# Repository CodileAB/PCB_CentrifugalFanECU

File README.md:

ECU for the Centrifugal Fan Module
==================================

This is the KiCad project for the ECU for the Centrifugal Fan module.

Licence
-------

Licenced under the CERN Open Hardware Licence v1.2.

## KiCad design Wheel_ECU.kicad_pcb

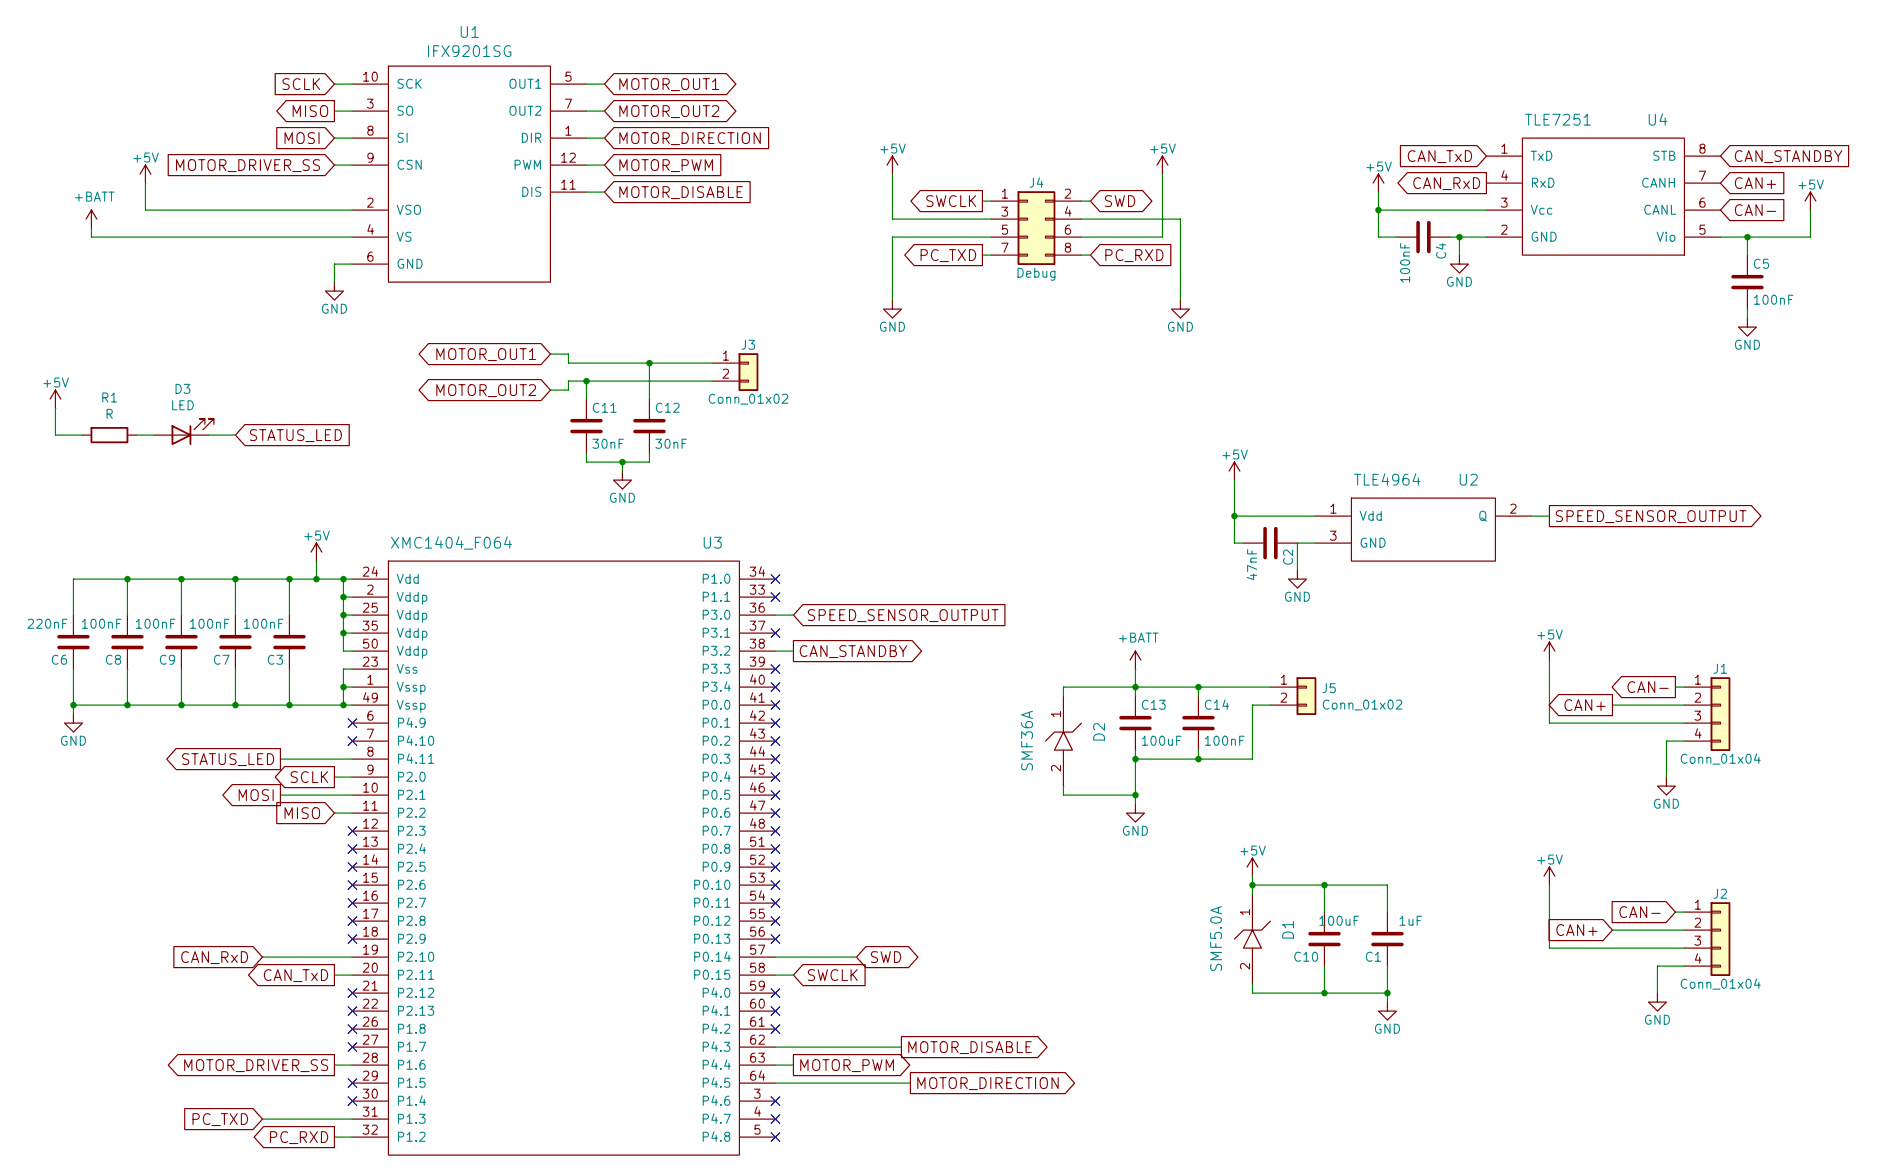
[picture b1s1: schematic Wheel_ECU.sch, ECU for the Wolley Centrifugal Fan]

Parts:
C1: 1uF; C_0805_HandSoldering
C2: 47nF; C_0805_HandSoldering
C3, C4, C5, C7, C8, C9, C14: 100nF; C_0805_HandSoldering
C6: 220nF; C_0805_HandSoldering
C10, C13: 100uF; C_0805_HandSoldering
C11, C12: 30nF; C_0805_HandSoldering
D1: SMF5.0A; D_SOD-123F
D2: SMF36A; D_SOD-123F
D3: LED; C_0805_HandSoldering
J1, J2: Conn_01x04; Pin_Header_Straight_1x04_Pitch2.54mm
J3, J5: Conn_01x02; PinHeader_1x02_P2.54mm_Vertical
J4: Debug; Pin_Header_Straight_2x04_Pitch2.54mm_SMD
R1: R; C_0805_HandSoldering
U1: IFX9201SG; SOIC-12_HeatSlugs
U2: TLE4964; TSOT-23_HandSoldering
U3: XMC1404_F064; TQFP-64_10x10mm_Pitch0.5mm_Handsoldering
U4: TLE7251; SOIC-8_3.9x4.9mm_Pitch1.27mm

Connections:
+5V: C1.2, C2.2, C3.2, C4.2, C5.1, C6.2, C7.2, C8.2, C9.2, C10.2, D1.1, J1.3, J2.3, J4.3, J4.6, R1.2, U1.2 (VSO), U2.1 (Vdd), U3.2 (Vddp), U3.24 (Vdd), U3.25 (Vddp), U3.35 (Vddp), U3.50 (Vddp), U4.3 (Vcc), U4.5 (Vio)
+BATT: C13.1, C14.1, D2.1, J5.1, U1.4 (VS)
CAN+: J1.2, J2.2, U4.7 (CANH)
CAN-: J1.1, J2.1, U4.6 (CANL)
CAN_RxD: U3.19 (P2.10), U4.4 (RxD)
CAN_STANDBY: U3.38 (P3.2), U4.8 (STB)
CAN_TxD: U3.20 (P2.11), U4.1 (TxD)
GND: C1.1, C2.1, C3.1, C4.1, C5.2, C6.1, C7.1, C8.1, C9.1, C10.1, C11.2, C12.2, C13.2, C14.2, D1.2, D2.2, J1.4, J2.4, J4.4, J4.5, J5.2, U1.6 (GND), U2.3 (GND), U3.1 (Vssp), U3.23 (Vss), U3.49 (Vssp), U4.2 (GND)
MISO: U1.3 (SO), U3.11 (P2.2)
MOSI: U1.8 (SI), U3.10 (P2.1)
MOTOR_DIRECTION: U1.1 (DIR), U3.64 (P4.5)
MOTOR_DISABLE: U1.11 (DIS), U3.62 (P4.3)
MOTOR_DRIVER_SS: U1.9 (CSN), U3.28 (P1.6)
MOTOR_OUT1: C12.1, J3.1, U1.5 (OUT1)
MOTOR_OUT2: C11.1, J3.2, U1.7 (OUT2)
MOTOR_PWM: U1.12 (PWM), U3.63 (P4.4)
unnamed: D3.2 (A), R1.1
PC_RXD: J4.8, U3.32 (P1.2)
PC_TXD: J4.7, U3.31 (P1.3)
SCLK: U1.10 (SCK), U3.9 (P2.0)
SPEED_SENSOR_OUTPUT: U2.2 (Q), U3.36 (P3.0)
STATUS_LED: D3.1 (K), U3.8 (P4.11)
SWCLK: J4.1, U3.58 (P0.15)
SWD: J4.2, U3.57 (P0.14)

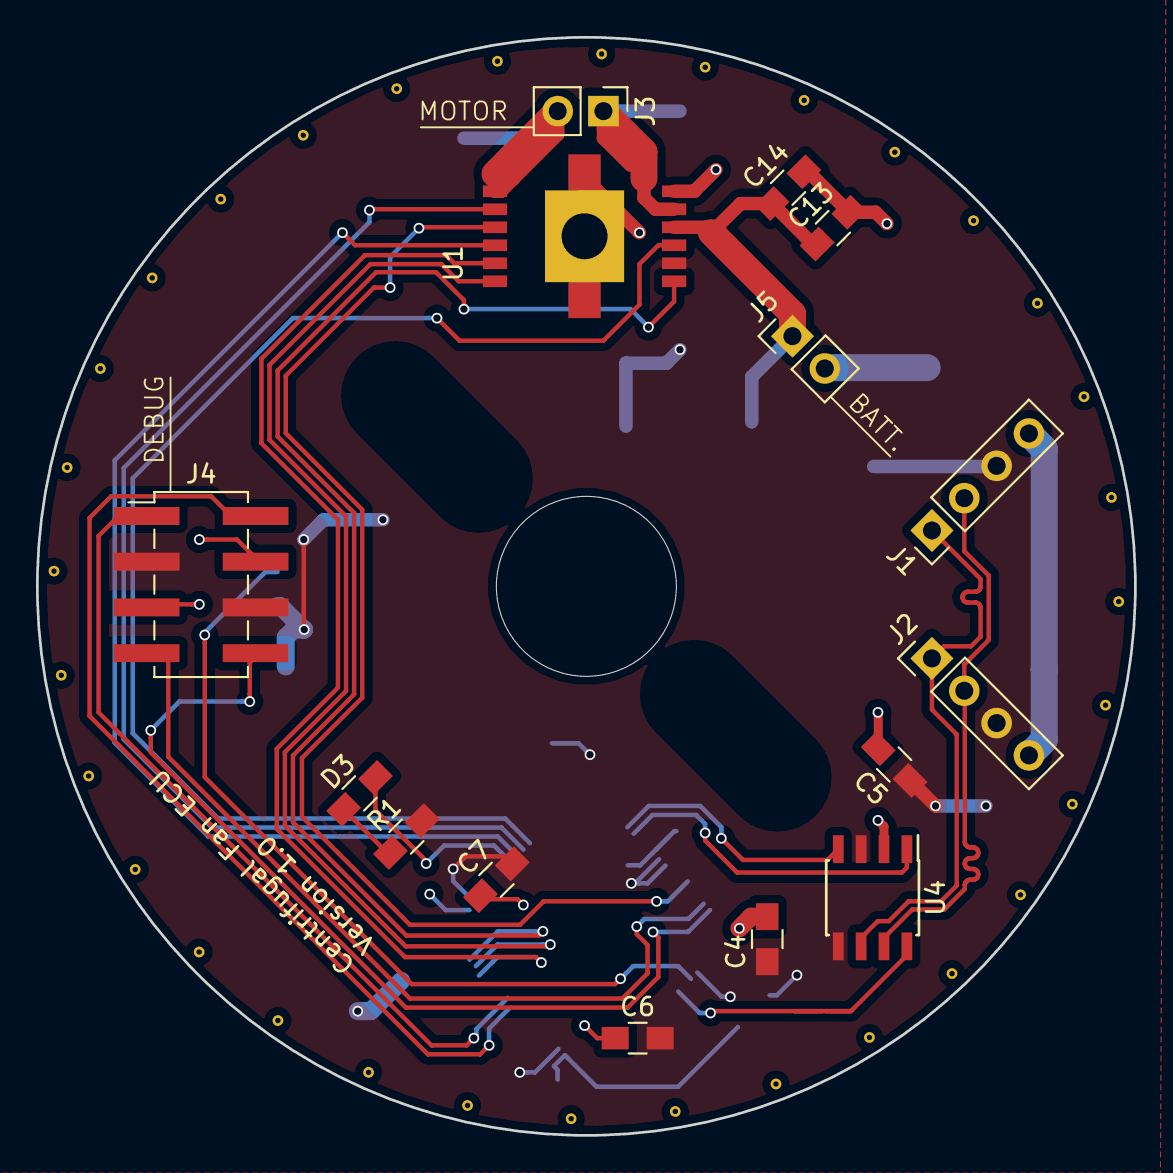
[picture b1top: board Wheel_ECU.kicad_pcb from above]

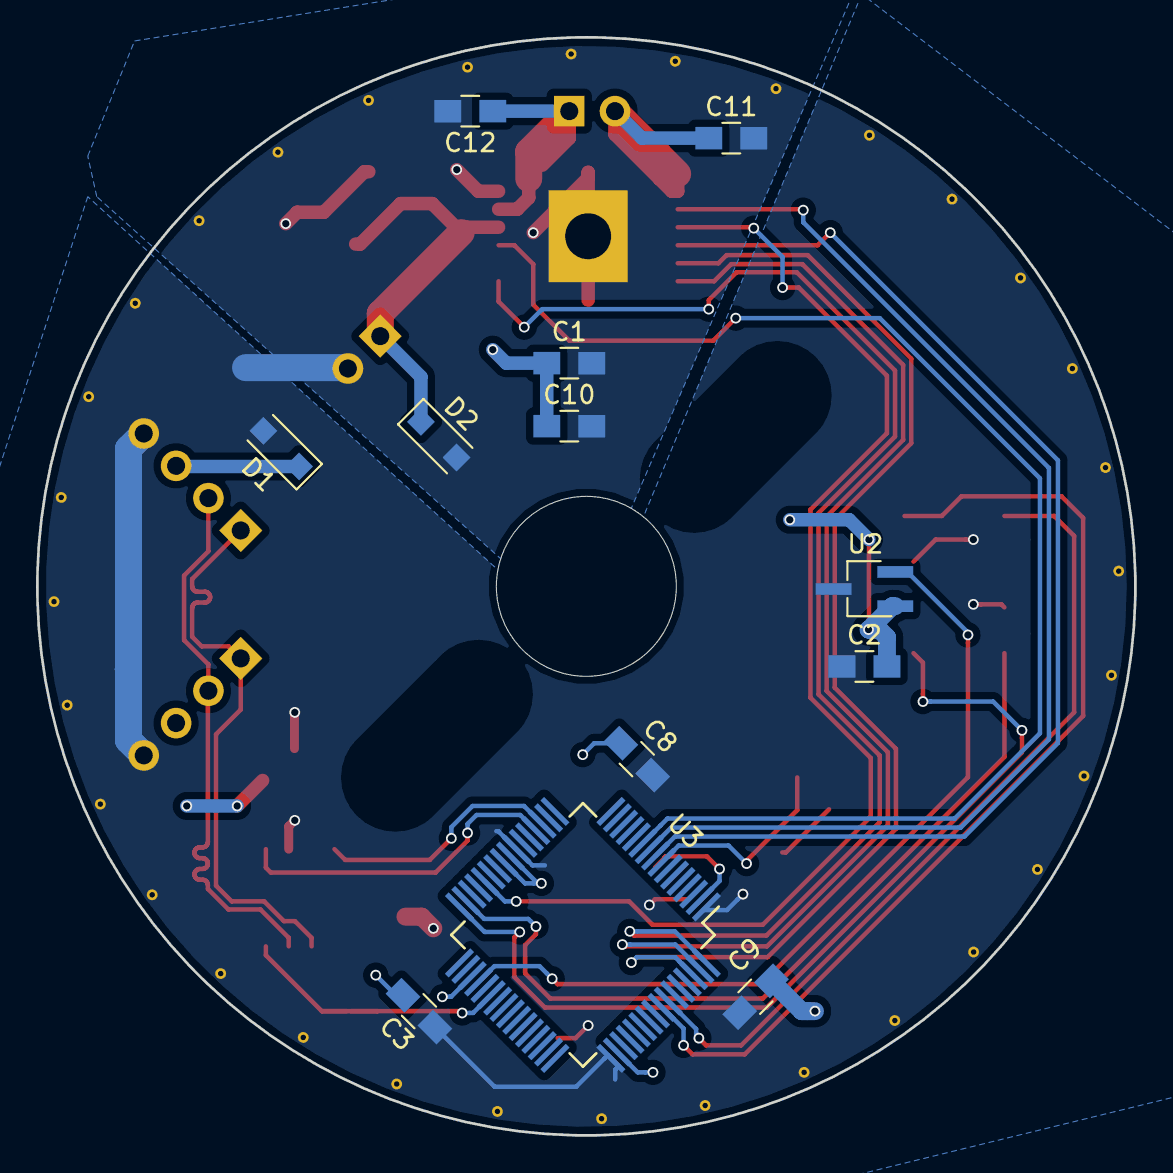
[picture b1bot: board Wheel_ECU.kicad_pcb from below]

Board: 2 copper layers, 61.0 x 61.0 mm, 30 parts (12 on the bottom side), 24 nets.

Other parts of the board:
M**: Motor_Center_Hole
M**#2, M**#3: Motor_Mount_Hole; Mount_Hole_M3x6.5

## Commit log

2021-02-12 Update document information after forking from PCB_StandardWheelECU
2021-02-12 Remove the Codile logotype from the PCB
2021-02-12 Move logotype
2021-02-12 Remove circle from PCB
2021-02-12 Increase the motor hole size to 10 mm
2021-02-12 Increase motor hole again and remove two mount holes
2021-02-13 Supply the motor directly from the battery
2021-02-13 Update the name and version text on the PCB
2021-02-13 Make room for a bigger motor on the PCB
2021-02-13 Improve the placement of the motor driver and connector
2021-02-13 Add labels for the motor and debug connectors
2021-02-14 Move out some vias from the motor area to avoid short circuits
2021-02-14 Add status LED
2021-02-14 Update date
2021-02-14 Add a temperature sensor (LM35D)
2021-02-26 Remove the gerber files
2021-02-26 Update the README
